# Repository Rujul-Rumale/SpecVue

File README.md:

# SpecVue

A 4-layer PCB for smart glasses featuring an ESP32-S3 with camera live streaming and on-device object classification over Wi-Fi.

## Overview

This board is a compact (90×17 mm) smart glasses controller designed around the ESP32-S3. It captures video from a parallel-interface camera module, runs a lightweight object classifier (e.g., TensorFlow Lite Micro / ESP-DL) on the ESP32-S3, and streams results (bounding boxes, labels) over Wi-Fi — optionally with live video. Li-Po battery powered with built-in charging.

### Block Diagram

```
USB-C ─┬─► MCP73831 (Charger) ──► Li-Po Battery
        │                              │
        └──► VSYS ◄────────────────────┘
               │
        ┌──────┼──────────┐
        │      │          │
   AMS1117  AP2121AK  LP2985
    3.3V      1.3V      2.8V
        │      │          │
   VDD_CPU  Core Rail  Camera IO
     & I/O    (1.3v)    (2.8v)

┌──────────────── Data Flow ────────────────┐

 Camera ──► ESP32-S3 ──┬─► TFLite Micro ──► Wi-Fi ──► Detected objects
 (DVP)      (capture)   │   (classifier)    (MQTT/UDP)
                        └─► Wi-Fi ──► Live video stream (optional)
```

### Specifications

| Parameter | Value |
|-----------|-------|
| Board dimensions | 90 mm × 17 mm |
| Layer count | 4 (F.Cu, In1.Cu, In2.Cu, B.Cu) |
| Board thickness | 1.6 mm |
| Copper weight | 1 oz (0.035 mm) all layers |
| Dielectric | FR4 (εr = 4.5) |
| Input power | USB VBUS (5 V) or Li-Po battery (3.7–4.2 V) |
| Charger current | 500 mA (set by R1 = 2 kΩ) |

## Power Tree

| Rail | Voltage | Regulator | Max Current | Supplies |
|------|---------|-----------|-------------|----------|
| VSYS | Battery / 5V | (direct from USB-Diode-BAT path) | — | Input to all regulators |
| 3.3 V | 3.3 V | AMS1117-3.3 (U4) | 800 mA | ESP32-S3 core + I/O, flash, mic |
| 1.3 V | 1.3 V | AP2121AK-1.3 (U6) | 400 mA | Camera core (1.3v rail) |
| 2.8 V | 2.8 V | LP2985-2.8 (U5) | 150 mA | Camera analog/digital IO (2.8v rail) |

### Power Path

1. **USB VBUS** feeds the MCP73831-2-OT (U3) Li-Po charger IC.
2. Battery connects through AO3401A (Q1) P-FET for reverse-polarity protection.
3. The FET's output (VSYS) is shared between USB and battery — no external power mux needed (Q1's body diode provides OR-ing).
4. VSYS powers all three LDOs in parallel.
5. SS14 (D4) Schottky diode provides additional input protection.

## Microcontroller

**ESP32-S3 (U1)**, QFN-56 7×7 mm, 0.4 mm pitch.

- Dual-core Xtensa LX7 @ up to 240 MHz
- Built-in Wi-Fi 802.11 b/g/n + BLE 5.0
- 512 kB SRAM, supports external PSRAM
- 40 MHz main crystal (Y2, 2520 package, 10 ppm) with 15 pF load caps
- CHIP_PU (pin 4) pulled high with a resistor, with reset button (Reset)

### GPIO Allocation

| GPIO(s) | Function | Connected To |
|---------|----------|-------------|
| GPIO4 | ADC / Battery monitor | Voltage divider on VBAT |
| GPIO10–16, GPIO38–40, GPIO47–48 | Camera parallel data bus | J4 FFC connector |
| GPIO17 | I2C SCL | J4 pin 5 (camera control) |
| GPIO18 | I2C SDA | J4 pin 4 (camera control) |
| GPIO0 | Boot mode selection | Flash button |
| GPIO46 | Strapping pin | Pull-up/pull-down resistors |
| U0TXD, U0RXD | Serial console | Debug UART |

**Note**: Several GPIOs (21, 33, 37, 41–46) are available for future expansion or current sensing.

## Memory

**W25Q128JVS (U2)** — 128 Mbit (16 MB) SPI flash, SOIC-8 package.

| ESP32-S3 Pin | Flash Pin | Net |
|-------------|-----------|-----|
| GPIO26 (SPICS0) | CS# | SPICS0 |
| GPIO27 (SPID) | DO/IO1 | SPID |
| GPIO28 (SPIQ) | DI/IO0 | SPIQ |
| GPIO29 (SPIWP) | WP#/IO2 | SPIWP |
| GPIO30 (SPIHD) | HOLD#/IO3 | SPIHD |
| GPIO31 (SPICLK) | CLK | SPISCK |

The ESP32-S3 uses its dedicated SPI2 controller for flash, with four I/O lines for Quad-SPI operation. The flash operates at 3.3 V from the VDD_CPU rail.

## Camera Interface

**J4** — Molex 5034802400, 24-pin 0.5 mm pitch FFC connector.

| Pin | Net | Typical Camera Function |
|-----|-----|------------------------|
| 1 | NC | — |
| 2, 22 | 2.8 V | AVDD (analog supply) |
| 3, 11 | GND | Ground |
| 4 | IO18/SDA | SCCB / I2C data |
| 5 | IO17/SCL | SCCB / I2C clock |
| 6 | IO16 | D0 (data bit 0) |
| 7 | IO15 | D1 |
| 8 | IO14 | D2 |
| 9 | IO13 | D3 |
| 10 | IO12 | D4 |
| 12 | IO11 | D5 |
| 13 | IO10 | D6 |
| 14 | IO48 | XCLK (camera master clock) |
| 15 | 2.8 V | DVDD (digital supply) |
| 16 | 1.3 V | DOVDD (core supply) |
| 17 | IO47 | D7 (data bit 7) |
| 18 | NC/Pull config | Camera ID / detection |
| 19 | IO38 | VSYNC (vertical sync) |
| 20 | Pull-down (10 kΩ) | PWDN (power-down, pulled low for normal operation) |
| 21 | IO39 | HREF / HSYNC (horizontal sync) |
| 23 | IO40 | PCLK (pixel clock) |
| 24 | (shared pull) | Reset / detection |

The pinout is compatible with OV2640/OV5640/GC2035 8-bit parallel (DVP) camera modules. The 1.3 V rail (core) and 2.8 V rails (analog + digital IO) match typical CMOS sensor requirements.

## Audio

**MP34DT05TR-A (U7)** — MEMS digital microphone, PDM output.

| Mic Pin | Net |
|---------|-----|
| VDD | 3.3 V (from AMS1117) |
| GND | GND |
| CLK | PDM clock from ESP32-S3 |
| DAT | PDM data to ESP32-S3 |
| LDO | Output from internal LDO (decoupled with 0.1 µF + 10 µF) |

The MP34DT05TR-A uses a 4-pin custom footprint. The PDM clock and data connect to ESP32-S3 GPIOs for audio capture alongside video streaming.

## USB-C

**J1** — USB-C receptacle, 14-pin (USB 2.0 only).

| Feature | Implementation |
|---------|---------------|
| CC1, CC2 | 5.1 kΩ pulldown (R17, R14) — sink-only, no PD |
| D+, D- | Series 33 Ω resistors for HS impedance matching |
| VBUS | Direct to charger input |
| SHIELD | Connected to GND via filter |

No SBU lines or e-marker chip — this is a straightforward USB 2.0 sink configuration.

## Battery Charger

**MCP73831-2-OT (U3)** — Single-cell Li-Po linear charger.

| Component | Value | Purpose |
|-----------|-------|---------|
| R1 | 2 kΩ | PROG resistor — sets charge current to 500 mA |
| STAT | LED (D1) | Charge status indicator — on during charging, off when done, blink for fault |

## Status LEDs

| LED | Color | Driven By | Function |
|-----|-------|-----------|----------|
| D1 | Red (0603) | MCP73831 STAT | Charging status — on during charging, off when done |
| D2 | (0603) | VDD_CPU via 470 Ω | Power indicator (always on when 3.3 V present) |
| D3 | (0603) | GPIO1 — ESP32-S3 | User indicator |

All LEDs have ~470 Ω series current-limiting resistors.

## Antenna

**AE1** — 2.4 GHz PCB antenna (TI SWRA117D reference design), left-edge placement.

This is a PCB trace antenna based on Texas Instruments application note SWRA117D. It uses an inverted-F or meandered PCB trace pattern on the board edge with a ground clearance keep-out area beneath it. The RF feed uses a pi-network (C20, C21, L6) for impedance matching. No separate antenna component is needed — the antenna is part of the PCB itself.

## PCB Stackup

| Layer | Material | Thickness | Type |
|-------|----------|-----------|------|
| Top solder mask | — | 0.01 mm | — |
| F.Cu | Copper | 0.035 mm | Signal + traces |
| Prepreg | FR4 (εr = 4.5) | 0.1 mm | — |
| In1.Cu | Copper | 0.035 mm | Signal routing |
| Core | FR4 | 1.24 mm | — |
| In2.Cu | Copper | 0.035 mm | Signal routing |
| Prepreg | FR4 (εr = 4.5) | 0.1 mm | — |
| B.Cu | Copper | 0.035 mm | Signal + traces |
| Bottom solder mask | — | 0.01 mm | — |

## Component Count

| Category | Count |
|----------|-------|
| Resistors (0402) | 17 |
| Capacitors (0402) | 36 |
| Inductors | 2 |
| ICs | 7 |
| Connectors | 3 (USB-C, FFC, pin header) |
| LEDs (0603) | 3 |
| Push buttons | 2 |
| Crystal | 1 |
| Antenna | 1 |
| Transistor (P-FET) | 1 |
| Test points | 2 |
| Schottky diode | 1 |
| **Total footprints** | **~76** |

## Getting Started

### Prerequisites

- **KiCad 9.x or later** (files saved with generator v9.0)
- A 24-pin 0.5 mm pitch FFC camera module (OV2640/OV5640 compatible)

### Opening the Project

```bash
git clone <repo-url>
cd SpecVue
# Open SpecVue.kicad_pro in KiCad
```

### First-Time Setup — Footprint Libraries

Two custom footprints live in the project root as `.kicad_mod` files. The first time you open the project, KiCad may show warnings like *"Footprint library 'FFC24' not found"*. This is expected — the footprint geometry is already embedded in the PCB (the board displays correctly), but the schematic-to-footprint link needs a library entry.

**To resolve (one-time setup):**

1. In KiCad, open **Preferences → Manage Footprint Libraries** (or **PCB Editor → Preferences → Footprint Libraries**)
2. Switch to the **Project** tab
3. Click **Add empty row** (folder+star icon) and configure each:

| Nickname | Library Path | Type |
|----------|-------------|------|
| `FFC24` | `./MOLEX_5034802400.kicad_mod` | `KiCad` |
| `footprints` | `./MP34DT05TR-A_STM.kicad_mod` (or use folder containing it) | `KiCad` |

Alternatively, use a single entry pointing to the project root:

| Nickname | Library Path | Type |
|----------|-------------|------|
| `Custom` | `./` (project directory) | `KiCad` |

Then update the footprints via **Tools → Update Footprints from Library** and reassign `FFC24:` and `footprints:` references to the new library.

(If you skip this step, the schematic will show footprint warnings, but the PCB opens and edits fine — the geometry is stored in the `.kicad_pcb` file.)

### Generating Gerbers

**File → Fabrication → Gerbers** in KiCad (no pre-built gerbers are committed).

### Bill of Materials

See [`SpecVue.csv`](./SpecVue.csv) — all components listed with DigiKey part numbers. Key ICs:

| Ref | Part | Package | DigiKey (or equivalent) |
|-----|------|---------|------------------------|
| U1 | ESP32-S3 | QFN-56 7×7 mm | Espressif |
| U2 | W25Q128JVS | SOIC-8 | W25Q128JVS |
| U3 | MCP73831-2-OT | SOT-23-5 | MCP73831T-2ATI/OT |
| U4 | AMS1117-3.3 | SOT-223 | AMS1117-3.3 |
| U5 | LP2985-2.8 | SOT-23-5 | LP2985-2.8DBVR |
| U6 | AP2121AK-1.3 | SOT-23-5 | AP2121AK-1.3TRG1 |
| U7 | MP34DT05TR-A | Custom (MEMS mic) | MP34DT05TR-A |
| J1 | USB-C (14-pin) | HC-TYPE-C-16P-01A | HCTL |
| J2 | Programming header | 1×02 pin header 2.54 mm | — |
| J4 | Molex 5034802400 | 24-pin FFC 0.5 mm | 5034802400 |
| Y2 | 40 MHz crystal | 2520 SMD 10 ppm | — |
| Q1 | AO3401A | SOT-23 | P-Channel MOSFET |
| D4 | SS14 | SMA | Schottky diode |

## Firmware Development

Use **ESP-IDF** or **Arduino-ESP32** with the ESP32-S3 target. Key framework integration points:

- Camera: `esp32-camera` library (8-bit DVP mode)
- Classification: TensorFlow Lite Micro or ESP-DL for on-device inference; output is label + confidence per frame
- Communication: Stream detected objects via MQTT or UDP to a companion app/server; optionally embed bounding boxes in a live video stream
- Audio: I2S peripheral in PDM mode for the MEMS mic
- Wi-Fi: ESP32 native Wi-Fi stack for video streaming and detection telemetry

## Board Dimensions

```
  ┌──────────────────────────────────┐
  │  90.00 mm                        │
  │                                  │
  │                                  │ 17.00 mm
  │                                  │
  └──────────────────────────────────┘
```

The 90×17 mm aspect fits within a standard glasses temple arm. No mounting holes — the board is intended to be secured by enclosure pressure or adhesive within the frame.

## License

This hardware design is released under the [CERN Open Hardware Licence Version 2 - Permissive](https://ohwr.org/cern_ohl_p_v2.txt) (`CERN-OHL-P-2.0`).

Copyright (c) 2026 Rujul Rumale.

You may use, study, modify, manufacture, and distribute this design and products made from it; you must retain the copyright and licence notices. See [LICENSE](LICENSE) for the full text.

---

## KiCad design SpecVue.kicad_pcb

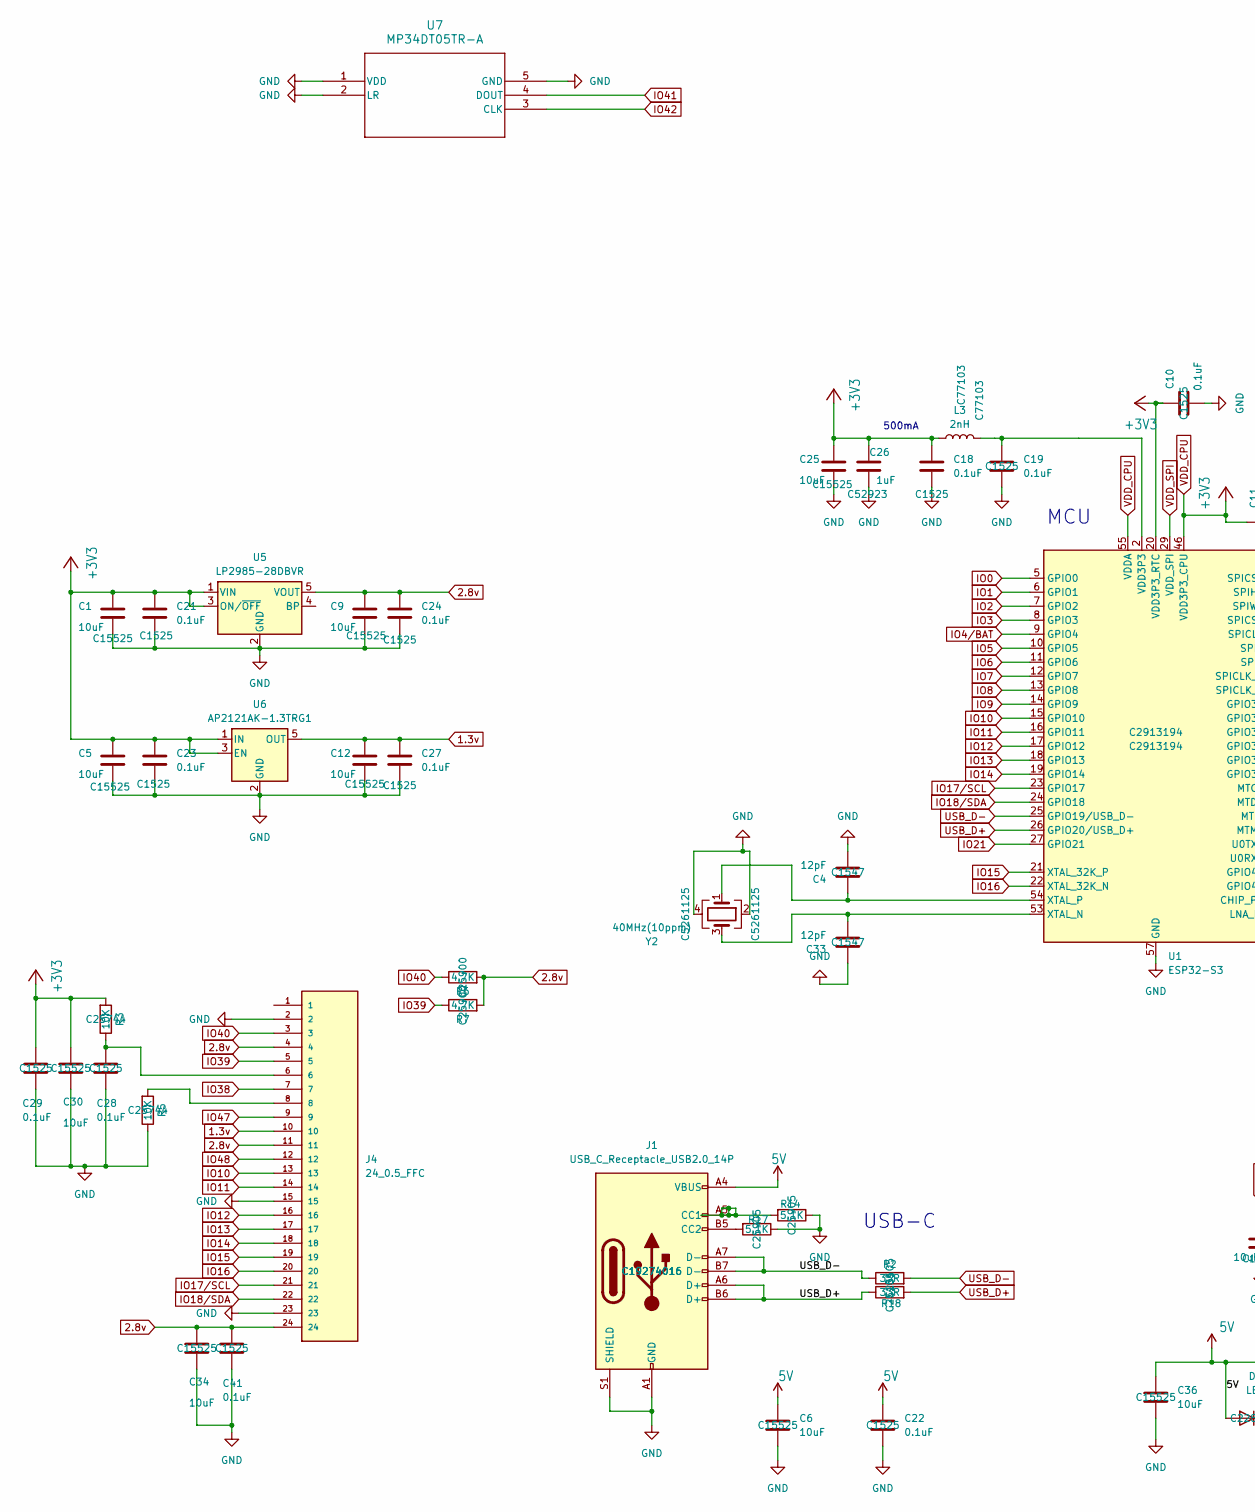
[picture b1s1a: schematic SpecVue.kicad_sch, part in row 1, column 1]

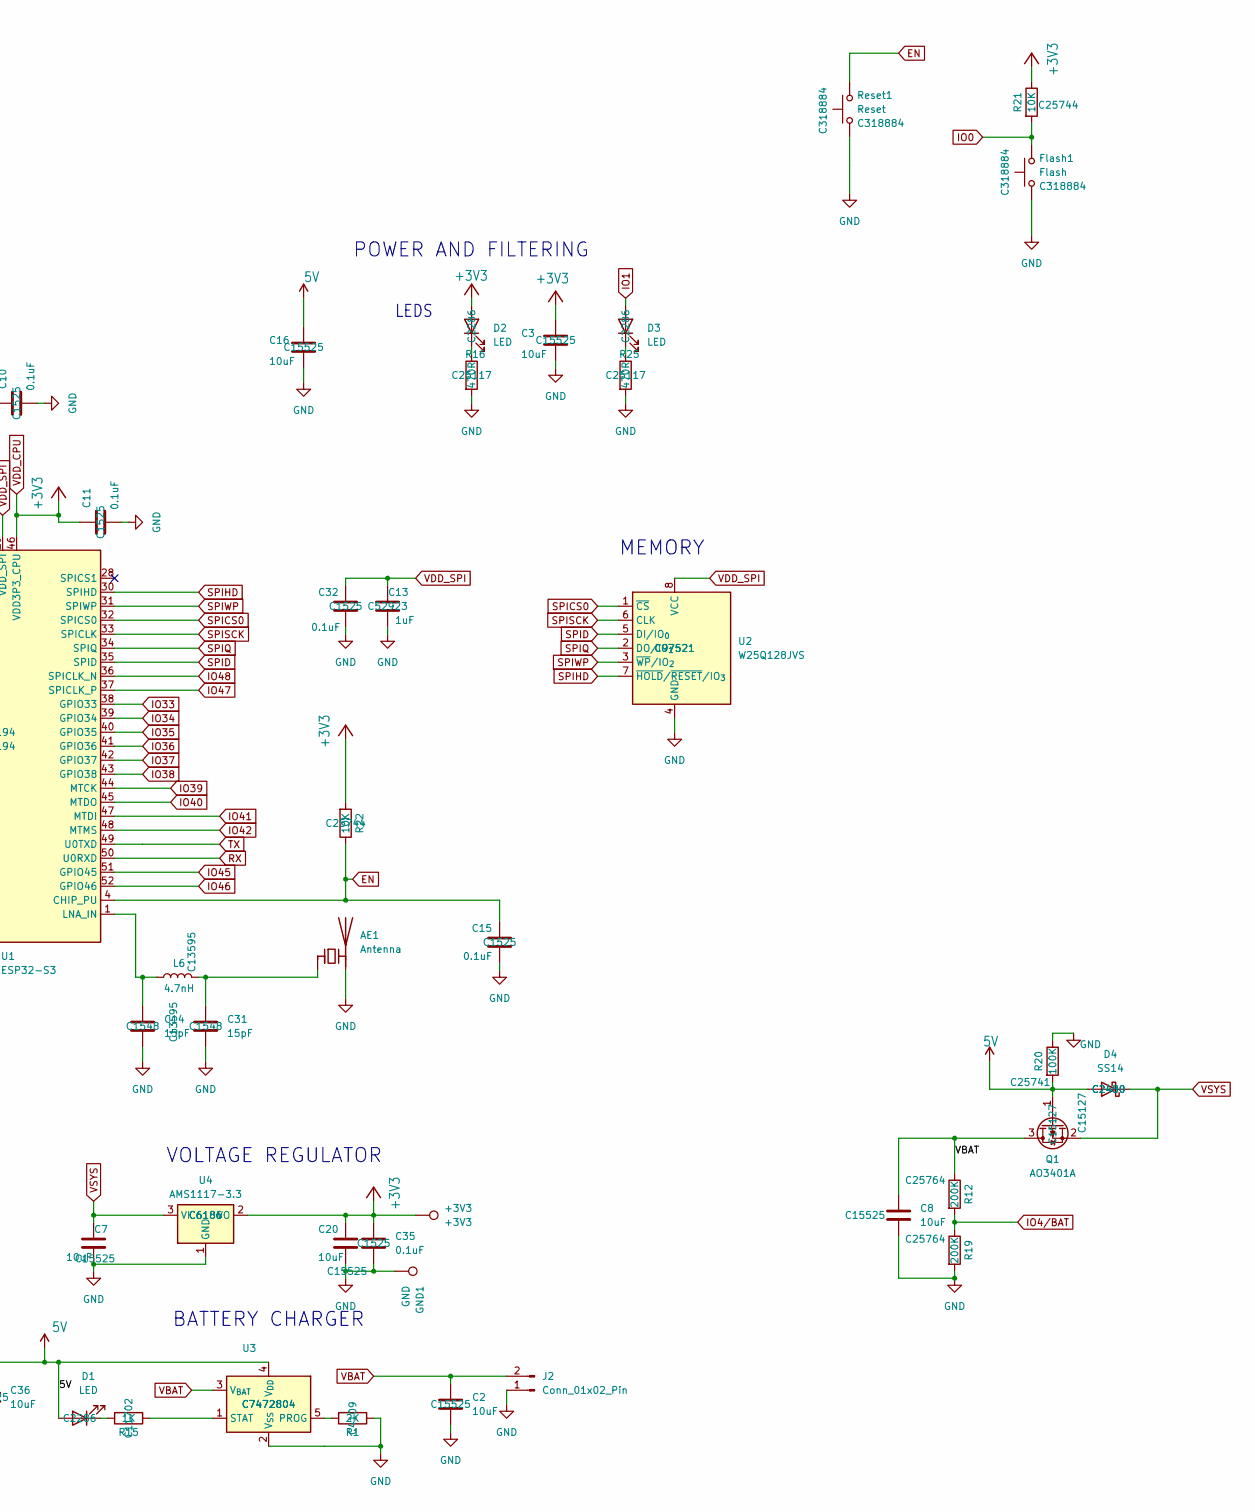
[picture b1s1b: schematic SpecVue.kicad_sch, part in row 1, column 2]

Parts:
+3V3: +3V3; TestPoint_Pad_D1.0mm
AE1: Antenna; Texas_SWRA117D_2.4GHz_Left
C1, C2, C3, C5, C6, C7, C8, C9, C12, C16, C20, C25, C30, C34, C36: 10uF; C_0402_1005Metric; MNF PART NUMBER C15525; LCSC C15525
C4, C33: 12pF; C_0402_1005Metric; MNF PART NUMBER C1547; LCSC C1547
C10, C11, C15, C18, C19, C21, C22, C23, C24, C27, C28, C29, C32, C35, C41: 0.1uF; C_0402_1005Metric; MNF PART NUMBER C1525; LCSC C1525
C13, C26: 1uF; C_0402_1005Metric; MNF PART NUMBER C52923; LCSC C52923
C14, C31: 15pF; C_0402_1005Metric; MNF PART NUMBER C1548; LCSC C1548
D1, D2, D3: LED; LED_0603_1608Metric; MNF PART NUMBER C2286; LCSC C2286
D4: SS14; D_SMA; MNF PART NUMBER C2480; LCSC C2480
Flash1: Flash; SW_Push_1P1T-SH_NO_CK_KMR2xxG; MNF PART NUMBER C318884; LCSC C318884
GND1: GND; TestPoint_Pad_D1.0mm
J1: USB_C_Receptacle_USB2.0_14P; USB_C_Receptacle_HCTL_HC-TYPE-C-16P-01A; MNF PART NUMBER C19274016; LCSC C19274016
J2: Conn_01x02_Pin; PinSocket_1x02_P2.54mm_Vertical
J4: 24_0.5_FFC; MOLEX_5034802400; PARTREV J
L3: 2nH; L_0402_1005Metric; MNF PART NUMBER C77103; LCSC C77103
L6: 4.7nH; L_0402_1005Metric; MNF PART NUMBER C13595; LCSC C13595
Q1: AO3401A; SOT-23; MNF PART NUMBER C15127; LCSC C15127
R1: 2K; R_0402_1005Metric; MNF PART NUMBER C4109; LCSC C4109
R2, R18: 33R; R_0402_1005Metric; MNF PART NUMBER C25105; LCSC C25105
R3, R5, R21, R22: 10K; R_0402_1005Metric; MNF PART NUMBER C25744; LCSC C25744
R6, R7: 4.7K; R_0402_1005Metric; MNF PART NUMBER C25744; LCSC C25900
R12, R19: 200K; R_0402_1005Metric; MNF PART NUMBER C25764; LCSC C25764
R14, R17: 5.1K; R_0402_1005Metric; MNF PART NUMBER C25905; LCSC C25905
R15: 1K; R_0402_1005Metric; MNF PART NUMBER C11702; LCSC C11702
R16, R25: 470R; R_0402_1005Metric; MNF PART NUMBER C25117; LCSC C25117
R20: 100K; R_0402_1005Metric; MNF PART NUMBER C25741; LCSC C25741
Reset1: Reset; SW_Push_1P1T-SH_NO_CK_KMR2xxG; MNF PART NUMBER C318884; LCSC C318884
U1: ESP32-S3; QFN-56-1EP_7x7mm_P0.4mm_EP4x4mm; MNF PART NUMBER C2913194; LCSC C2913194
U2: W25Q128JVS; SOIC-8_5.3x5.3mm_P1.27mm; MNF PART NUMBER C97521; LCSC C97521
U3: MCP73831-2-OT; SOT-23-5; MNF PART NUMBER C7472804; LCSC C7472804
U4: AMS1117-3.3; SOT-223-3_TabPin2; MNF PART NUMBER C6186; LCSC C6186
U5: LP2985-28DBVR; SOT-23-5
U6: AP2121AK-1.3TRG1; SOT-23-5
U7: MP34DT05TR-A; MP34DT05TR-A_STM
Y2: 40MHz(10ppm); Crystal_SMD_2520-4Pin_2.5x2.0mm; MNF PART NUMBER C5261125; LCSC C5261125

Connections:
1.3v: C12.1, C27.1, J4.10, U6.5 (OUT)
2.8v: C9.1, C24.1, C34.1, C41.1, J4.4, J4.11, J4.24, R6.2, R7.2, U5.5 (VOUT)
5V: C6.1, C16.1, C22.1, C36.1, D1.2 (A), D4.2 (A), J1.A4 (VBUS), J1.A9 (VBUS), J1.B4 (VBUS), J1.B9 (VBUS), Q1.1 (G), R20.2, U3.4 (V_{DD})
EN: C15.1, R22.1, Reset1.2, U1.4 (CHIP_PU); also elsewhere on the board
GND: AE1.2 (PCB_Trace), C1.2, C2.2, C3.2, C4.2, C5.2, C6.2, C7.2, C8.2, C9.2, C10.2, C11.2, C12.2, C13.2, C14.2, C15.2, C16.2, C18.2, C19.2, C20.2, C21.2, C22.2, C23.2, C24.2, C25.2, C26.2, C27.2, C28.2, C29.2, C30.2, C31.2, C32.2, C33.1, C34.2, C35.2, C36.2, C41.2, Flash1.1, GND1.1, J1.A1 (GND), J1.A12 (GND), J1.B1 (GND), J1.B12 (GND), J1.S1 (SHIELD), J2.1, J4.2, J4.15, J4.23, R1.1, R5.1, R14.1, R16.2, R17.1, R19.2, R20.1, R25.2, Reset1.1, U1.57 (GND), U2.4 (GND), U3.2 (V_{SS}), U4.1 (GND), U5.2 (GND), U6.2 (GND), U7.1 (VDD), U7.2 (LR), U7.5 (GND), Y2.2, Y2.4; also elsewhere on the board
IO0: Flash1.2, R21.2, U1.5 (GPIO0); also elsewhere on the board
IO1: D3.2 (A), U1.6 (GPIO1)
IO2: U1.7 (GPIO2)
IO3: U1.8 (GPIO3)
IO4/BAT: R12.2, R19.1, U1.9 (GPIO4)
IO5: U1.10 (GPIO5)
IO6: U1.11 (GPIO6)
IO7: U1.12 (GPIO7)
IO8: U1.13 (GPIO8)
IO9: U1.14 (GPIO9)
IO10: J4.13, U1.15 (GPIO10)
IO11: J4.14, U1.16 (GPIO11)
IO12: J4.16, U1.17 (GPIO12)
IO13: J4.17, U1.18 (GPIO13)
IO14: J4.18, U1.19 (GPIO14)
IO15: J4.19, U1.21 (XTAL_32K_P)
IO16: J4.20, U1.22 (XTAL_32K_N)
IO17/SCL: J4.21, U1.23 (GPIO17)
IO18/SDA: J4.22, U1.24 (GPIO18)
IO21: U1.27 (GPIO21)
IO33: U1.38 (GPIO33)
IO34: U1.39 (GPIO34)
IO35: U1.40 (GPIO35)
IO36: U1.41 (GPIO36)
IO37: U1.42 (GPIO37)
IO38: J4.7, U1.43 (GPIO38)
IO39: J4.5, R7.1, U1.44 (MTCK)
IO40: J4.3, R6.1, U1.45 (MTDO)
IO41: U1.47 (MTDI), U7.4 (DOUT)
IO42: U1.48 (MTMS), U7.3 (CLK)
IO45: U1.51 (GPIO45)
IO46: U1.52 (GPIO46)
IO47: J4.9, U1.37 (SPICLK_P)
IO48: J4.12, U1.36 (SPICLK_N)
unnamed: AE1.1 (FEED), C31.1, L6.2
unnamed: C19.1, L3.2, U1.2 (VDD3P3), U1.3 (VDD3P3)
unnamed: C28.1, J4.6, R3.1
unnamed: D1.1 (K), R15.2
unnamed: D2.1 (K), R16.1
unnamed: D3.1 (K), R25.1
unnamed: J1.A5 (CC1), R14.2
unnamed: J1.B5 (CC2), R17.2
unnamed: J4.8, R5.2
unnamed: C14.1, L6.1, U1.1 (LNA_IN)
unnamed: C33.2, U1.53 (XTAL_N), Y2.3
unnamed: C4.1, U1.54 (XTAL_P), Y2.1
unnamed: R1.2, U3.5 (PROG)
unnamed: R15.1, U3.1 (STAT)
RX: U1.50 (U0RXD)
SPICS0: U1.32 (SPICS0), U2.1 (~CS)
SPID: U1.35 (SPID), U2.5 (DI/IO_{0})
SPIHD: U1.30 (SPIHD), U2.7 (~HOLD/~RESET/IO_{3})
SPIQ: U1.34 (SPIQ), U2.2 (DO/IO_{1})
SPISCK: U1.33 (SPICLK), U2.6 (CLK)
SPIWP: U1.31 (SPIWP), U2.3 (~WP/IO_{2})
TX: U1.49 (U0TXD)
USB_D+: J1.A6 (D+), J1.B6 (D+), R18.1, R18.2, U1.26 (GPIO20/USB_D+)
USB_D-: J1.A7 (D-), J1.B7 (D-), R2.1, R2.2, U1.25 (GPIO19/USB_D-)
VBAT: C2.1, C8.1, J2.2, Q1.3 (D), R12.1, U3.3 (V_{BAT})
VDD_CPU: +3V3.1, C1.1, C3.1, C5.1, C10.1, C11.1, C18.1, C20.1, C21.1, C23.1, C25.1, C26.1, C29.1, C30.1, C35.1, D2.2 (A), L3.1, R3.2, R21.1, R22.2, U1.20 (VDD3P3_RTC), U1.46 (VDD3P3_CPU), U1.55 (VDDA), U1.56 (VDDA), U4.2 (VO), U5.1 (VIN), U5.3 (ON/~OFF), U6.1 (IN), U6.3 (EN)
VDD_SPI: C13.1, C32.1, U1.29 (VDD_SPI), U2.8 (VCC)
VSYS: C7.1, D4.1 (K), Q1.2 (S), U4.3 (VI)

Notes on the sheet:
BATTERY CHARGER
VOLTAGE REGULATOR
500mA
LEDS
MCU
MEMORY
POWER AND FILTERING
USB-C

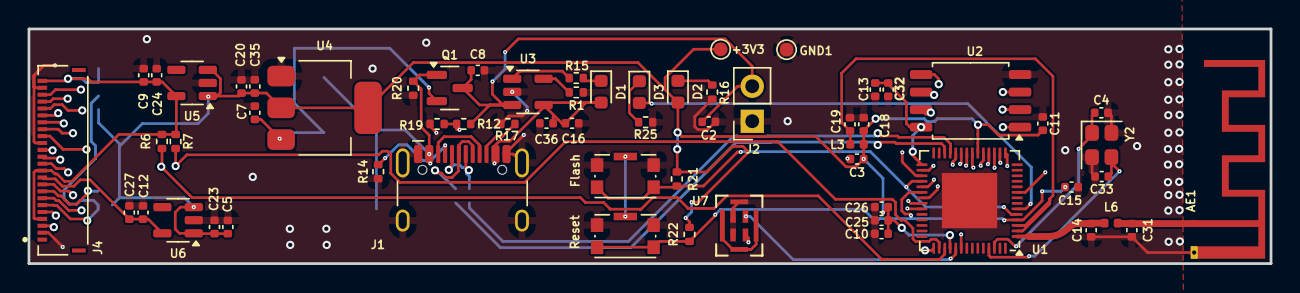
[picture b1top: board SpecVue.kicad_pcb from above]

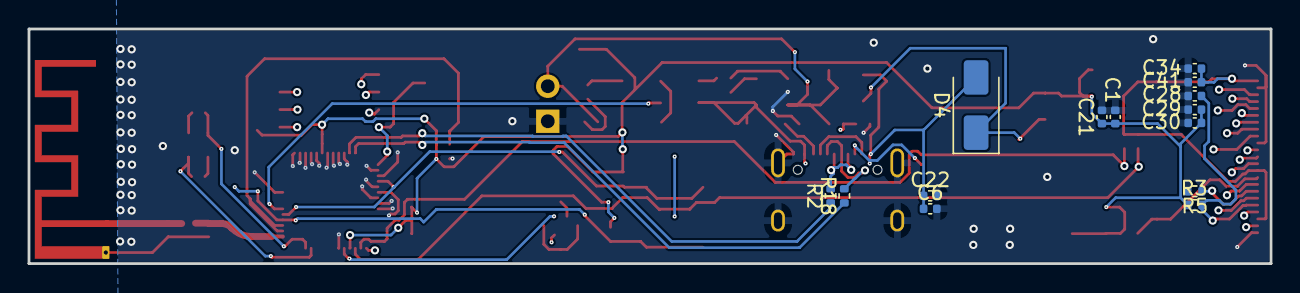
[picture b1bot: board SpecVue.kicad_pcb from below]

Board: 4 copper layers, 90.0 x 17.0 mm, 76 parts (14 on the bottom side), 50 nets.

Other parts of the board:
Flash: Flash; SW_Push_1P1T-SH_NO_CK_KMR2xxG
Reset: Reset; SW_Push_1P1T-SH_NO_CK_KMR2xxG

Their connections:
EN: Reset.2; also elsewhere on the board
GND: Flash.1, Reset.1; also elsewhere on the board
IO0: Flash.2; also elsewhere on the board
